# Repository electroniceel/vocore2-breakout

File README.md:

Breakout board for VoCore2 CPU module
=====================================

|  |  |

Main Features
-------------

- Uses a bare [VoCore2 CPU module](https://vocore.io/v2.html)
- core components on board
  - 1x RJ45 10/100 Ethernet
  - 1x USB-Host
  - 1x microSD
  - 12 VDC in with Buck-converter to 5V
  - RTC (MicroCrystal RV-8803-C7) and CR2032 battery
  - TCN75A or similar I2C temperature sensor
- Other pins broken out to 2.54mm pin headers (2x20)
- Separate pin headers for the console (UART2), protected by 74LVC2G17 buffer

Layout & Schematics
-------------------

See the ["kicad" directory](https://github.com/electroniceel/vocore2-breakout/tree/master/kicad).

There is also a [PDF version of the schematics](https://github.com/electroniceel/vocore2-breakout/raw/master/schematics.pdf) available.

Parts
-----

See the KiCad part data in the schematics and the linked footprints.

The only non-obvious part is the microSD socket. It is a common model found at Chinese suppliers.
The insertion/removal type is push-push (push-in, push-out).

It goes under various names and model numbers, often called "TF" or "TransFlash". Sometimes you
find more detailed numbers, like "TF09-2-12B" or "TF-01A".

You can get them from for example these offers:
- https://lcsc.com/product-detail/Connector-Card-Sockets_Korean-Hroparts-Elec-TF-01A_C91145.html
- https://www.aliexpress.com/item//32603008211.html
- https://www.aliexpress.com/item//32637213532.html

No warranties for correctness of these offers.

Solderbridges
-------------

The board contains two sets of solderbridges to select between features:

#### J3 & J4

You can select to which I2C bus to connect the onboard I2C components like RTC and temperature sensor.

You can select between 
1. the hardware I2C of the MT76x8, pins I2C_SD and I2C_CLK
2. a software emulated I2C bus on GPIO39 and GPIO40, using the driver i2c-gpio

#### J5 & J6

Select if you want the USB bus on the USB-A-Socket at the edge of the board or on the pin headers.
The USB bus shouldn't be connected to both because of reflections on the stub traces.

OpenWRT patches
---------------

- OpenWRT upstream already contains support for the VoCore2
- But the Device Tree there is a bit "sparse" and some features are disabled
- So I have created a new Target Profile called "VoCore2-Breakout" and some small adaptions to make the features work
- You can find this work in the ["openwrt" directory](https://github.com/electroniceel/vocore2-breakout/tree/master/openwrt)
- Use either the 0003a- or 0003b- patch based on how the solderbridges J3 & J4 are set

To use these:
1. First prepare the OpenWRT build system as described in https://openwrt.org/docs/guide-developer/build-system/start
2. Apply my patches before running "make menuconfig"
3. Select Target "MediaTek Ralink MIPS", Subtarget "MT76x8 based boards", Target Profile "VoCore2-Breakout"
4. Build

License
-------

This work is licensed under a [Creative Commons Attribution 4.0 International License](https://creativecommons.org/licenses/by/4.0/).

Please link to https://git.io/fpKW4 for attribution.

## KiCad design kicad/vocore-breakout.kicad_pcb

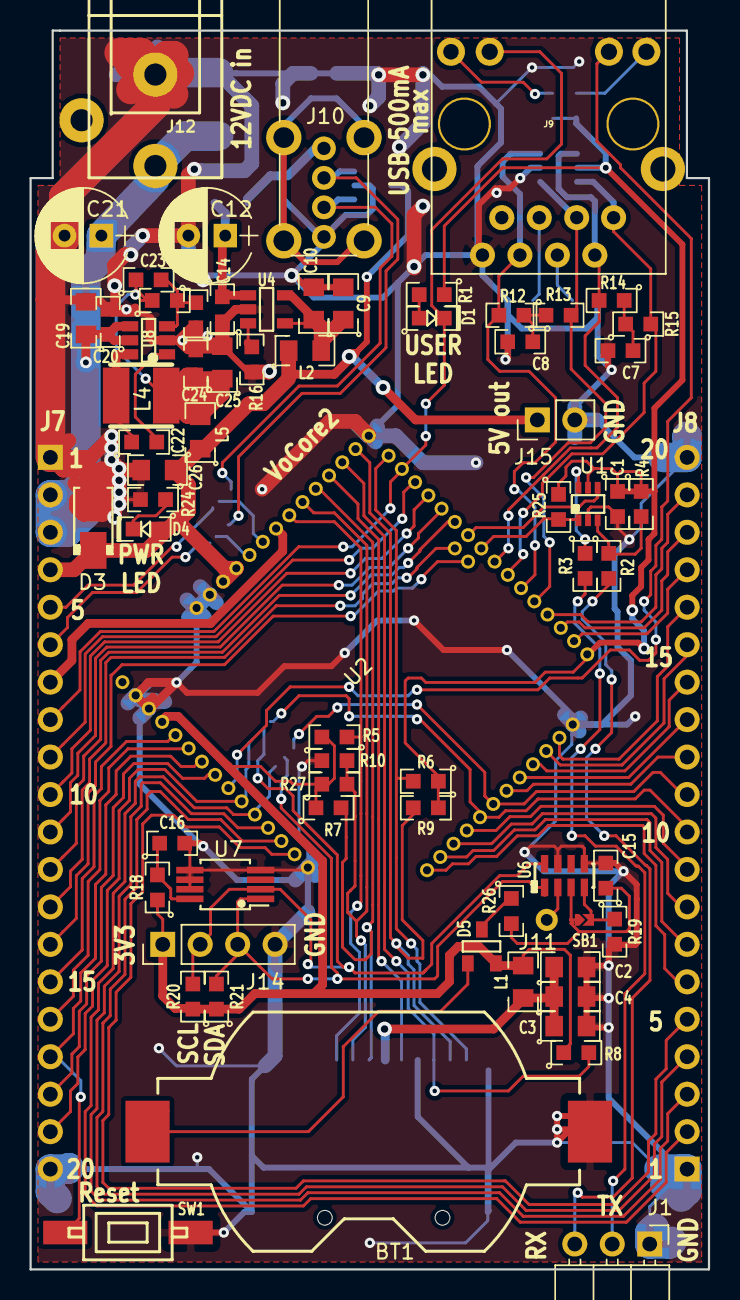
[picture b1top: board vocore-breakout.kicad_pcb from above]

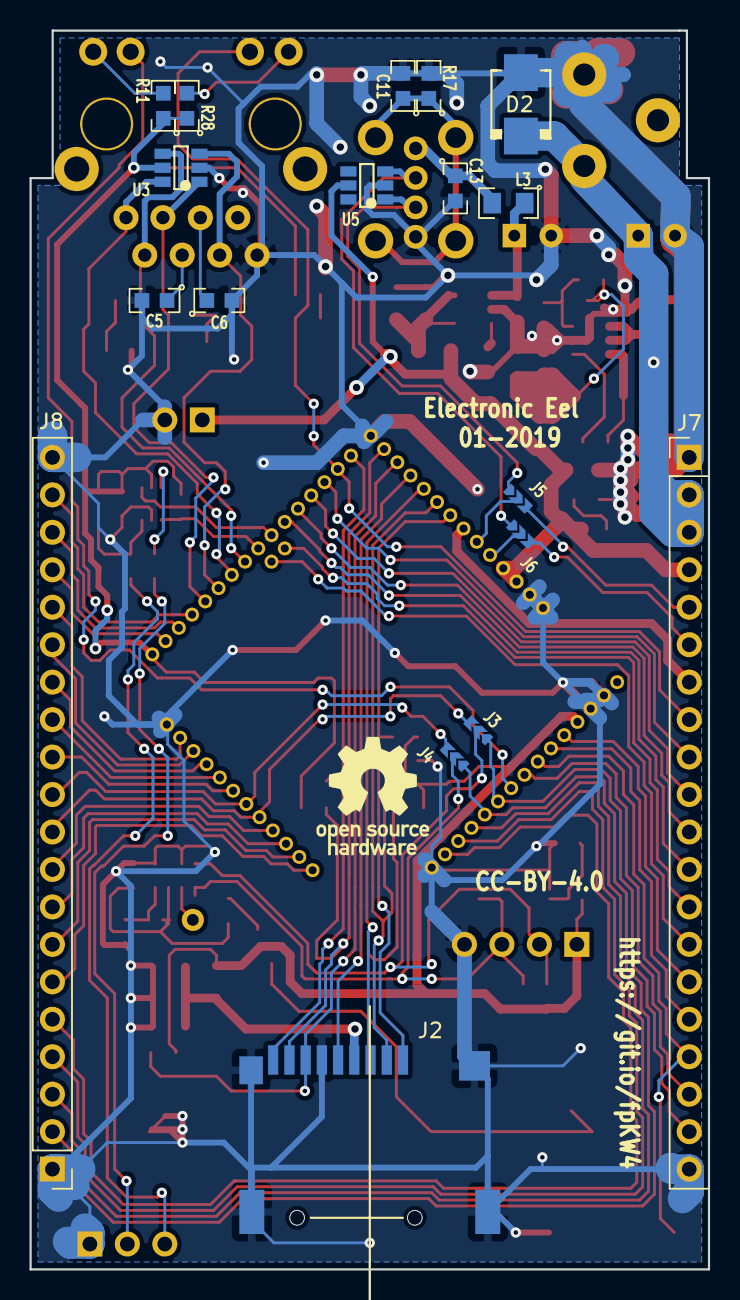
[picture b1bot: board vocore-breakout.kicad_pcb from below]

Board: 2 copper layers, 46.0 x 84.0 mm, 87 parts (18 on the bottom side), 84 nets.

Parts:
BT1: CR2032; SMTU2032-LF-CoinCell
C1, C5, C6, C7, C8, C13, C14, C15, C20, C22, C24: 100nF; SMD0603-wide-C
C2, C3, C4: 10µF; SMD0805-wide-C
C9, C10, C19, C25, C26: 4.7µF; SMD0805-wide-C
C11: 10nF; SMD0603-wide-C
C12, C21: 150µF; CP_Radial_D6.3mm_P2.50mm
C16: 1µF; SMD0603-wide-C
C23: 22pF; SMD0603-wide-C
D1: USER_LED; SMD0603-wide-diode
D2: SMBJ12A; SMB_Diode
D3: SMAJ5A; SMA_Diode
D4: Power LED; SMD0603-wide-diode
D5: BAS70-05; SOT-23
J1: Conn_01x03; Pin_Header_Angled_1x03_Pitch2.54mm
J2: Micro_SD_Card_Det; microSD-Receptacle-SelfEject
J3, J4, J5, J6: GS3; Solderbridge-3pad
J7, J8: Conn_01x20; Pin_Header_Straight_1x20_Pitch2.54mm
J9: HR911105_RJ45; RJ45-HR911105A
J10: USB_A; USB_A_Vertical_THT
J11: TST; Measurement_Point_Round-TH_Small
J12: Barrel_Jack; Cliff_FCR681465P_barrel_jack
J14: Conn_01x04; Pin_Header_Straight_1x04_Pitch2.54mm
J15: Conn_01x02; Pin_Header_Straight_1x02_Pitch2.54mm
L1, L2: 820nH; SMD0805-wide
L3, L5: Ferrite_Bead_Small; SMD0805-wide
L4: 4.7µH; Fastron-1616FPS
R1, R11, R28: 1K; SMD0603-wide-R
R2, R3, R18, R26: 100R; SMD0603-wide-R
R4, R5, R6, R7, R8, R9, R16, R19, R25, R27: 10K; SMD0603-wide-R
R10: DNP; SMD0603-wide-R
R12, R13, R14, R15: 49.9R; SMD0603-wide-R
R17: 1M; SMD0603-wide-R
R20, R21: 4.7K; SMD0603-wide-R
R22: 120K; SMD0603-wide-R
R23: 16K; SMD0603-wide-R
R24: 3.3K; SMD0603-wide-R
SB1: Solderbridge
SW1: RESET_BTN; Push-Button-SMD-6.0x3.5mm
U1: 74LVC2G17; SC-70-6-wide
U2: VoCore_v2
U3, U5: IP4220CZ6; SOT-23-6
U4: MT9700; SOT-23-5
U6: RV-8803; MicroCrystal-C7
U7: MCP9808; MSOP-8-wide
U8: SY8113B; SOT-23-6

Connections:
+3V3: C1.1, D5.2, J7.7, J14.1, L1.2, R1.1, R4.1, R5.1, R6.1, R7.1, R8.1, R9.1, R11.1, R18.1, R20.1, R21.1, R25.1, R27.1, R28.1, U1.5, U2.1, U2.26, U2.36, U3.5
+5V: C26.1, D3.1, D4.2, J7.4, J15.1, L2.1, L5.1, U2.29, U2.30, U5.5
+12V: C19.1, C20.1, C21.1, D2.1, J7.2, J7.3, J12.1, U8.4, U8.5
/GPIO37: J7.15, U2.37
/GPIO38: J7.16, U2.38
/GPIO39: J3.1, J7.19, U2.42
/GPIO40: J4.1, J8.2, U2.43
/GPIO41: J8.3, U2.44
/GPIO42: J7.18, U2.40
/I2C_CLK: J3.3, J8.10, U2.52
/I2C_SD: J4.3, J8.11, U2.53
/I2S_CLK: J8.9, U2.51
/I2S_SDI: J8.7, U2.49
/I2S_SDO: J8.6, U2.48
/I2S_WS: J8.8, U2.50
/NRST: J7.17, SW1.1, U2.39
/P2RN: J7.11, U2.14
/P2RP: J7.12, U2.13
/P2TN: J7.9, U2.16
/P2TP: J7.10, U2.15
/PWM0: J7.14, U2.11
/PWM1: J7.13, U2.12
/REFCLK: J8.19, U2.4
/RXD0: J8.18, U2.3
/RXD1: J8.5, U2.46
/SPI_CLK: J8.15, U2.57
/SPI_CS0: J8.16, U2.58
/SPI_CS1: J8.12, U2.54
/SPI_MISO: J8.14, U2.56
/SPI_MOSI: J8.13, U2.55
/SYS_I2C/SYS_SCL: J3.2, J14.2, R20.2, U6.8, U7.2
/SYS_I2C/SYS_SDA: J4.2, J14.3, R21.2, U6.1, U7.1
/SYS_I2C/Vdd_RTC: C15.1, R26.2, SB1.1, U6.3
/TXD0: J8.17, U2.2
/TXD1: J8.4, U2.45
/USB_DM_PIN: J6.3, J7.6
/USB_DP_PIN: J5.3, J7.5
/USER_LED: D1.1, J7.8, J9.11, U2.17
/ethernet/ETH_RN: J9.6, R12.2, U2.6, U3.3
/ethernet/ETH_RP: J9.3, R13.2, U2.5, U3.1
/ethernet/ETH_TN: J9.2, R14.2, U2.8, U3.4
/ethernet/ETH_TP: J9.1, R15.2, U2.7, U3.6
/ethernet/LINK_LED: J9.10, U2.41
/usb/USB_DN: J6.1, J10.2, U5.3
/usb/USB_DP: J5.1, J10.3, U5.1
GND: BT1.2, C1.2, C2.2, C3.2, C4.2, C5.2, C6.2, C7.2, C8.2, C9.2, C10.2, C11.2, C12.2, C13.2, C14.2, C15.2, C16.2, C19.2, C20.2, C21.2, C24.2, C25.2, C26.2, D2.2, D3.2, J1.1, J2.6, J2.11, J7.1, J7.20, J8.1, J8.20, J9.8, J10.4, J12.2, J14.4, J15.2, R10.2, R16.2, R17.2, R19.2, R23.2, R24.2, SW1.2, U1.2, U2.19, U2.31, U2.32, U2.34, U2.35, U2.47, U2.59, U3.2, U4.2, U5.2, U6.5, U6.7, U7.4, U7.5, U7.6, U7.7, U8.2
unnamed: BT1.1, D5.1
unnamed: C2.1, C3.1, C4.1, J2.4, L1.1
unnamed: C5.1, J9.4
unnamed: C6.1, J9.5
unnamed: C7.1, R14.1, R15.1
unnamed: C8.1, R12.1, R13.1
unnamed: C9.1, C10.1, L2.2, U4.4, U4.5
unnamed: C11.1, J10.5, R17.1
unnamed: C12.1, C14.1, L3.1, U4.1
unnamed: C13.1, J10.1, L3.2
unnamed: C16.1, R18.2, U7.8
unnamed: C22.1, L4.2, U8.6
unnamed: C22.2, U8.1
unnamed: C23.1, C24.1, C25.1, L4.1, L5.2, R22.1
unnamed: C23.2, R22.2, R23.1, U8.3
unnamed: D1.2, R1.2
unnamed: D4.1, R24.1
unnamed: D5.3, R26.1
unnamed: J1.2, R3.2
unnamed: J1.3, R2.2
unnamed: J2.1, R5.2, U2.25
unnamed: J2.2, R10.1, R27.2, U2.24
unnamed: J2.3, R7.2, U2.23
unnamed: J2.5, U2.22
unnamed: J2.7, R8.2, U2.21
unnamed: J2.8, R9.2, U2.20
unnamed: J2.9, R6.2, U2.18
unnamed: J5.2, U2.27
unnamed: J6.2, U2.28
unnamed: J9.9, R11.2
unnamed: J9.12, R28.2
unnamed: J11.1, U6.2
unnamed: R2.1, R4.2, U1.3
unnamed: R3.1, U1.6
unnamed: R16.1, U4.3
unnamed: R19.1, SB1.2, U6.4
unnamed: R25.2, U1.1, U2.9
unnamed: U1.4, U2.10

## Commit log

2019-01-08 import kicad project
2019-01-08 add photos
2019-01-08 Initial readme
2019-01-08 fix readme
2019-01-08 add license file (CC-BY-4.0)
2019-01-08 try to link the highres images in the README
2019-01-08 fix typo in the link
2019-01-08 add openwrt patches
2019-01-08 add note about alternative patches 0003a/b
2019-03-24 add ready-to-order gerbers
